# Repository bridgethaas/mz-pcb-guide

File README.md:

# mz-pcb-guide

Products of following along with the 'Designing a keyboard from scratch' guide at https://www.masterzen.fr/2020/05/03/designing-a-keyboard-part-1/

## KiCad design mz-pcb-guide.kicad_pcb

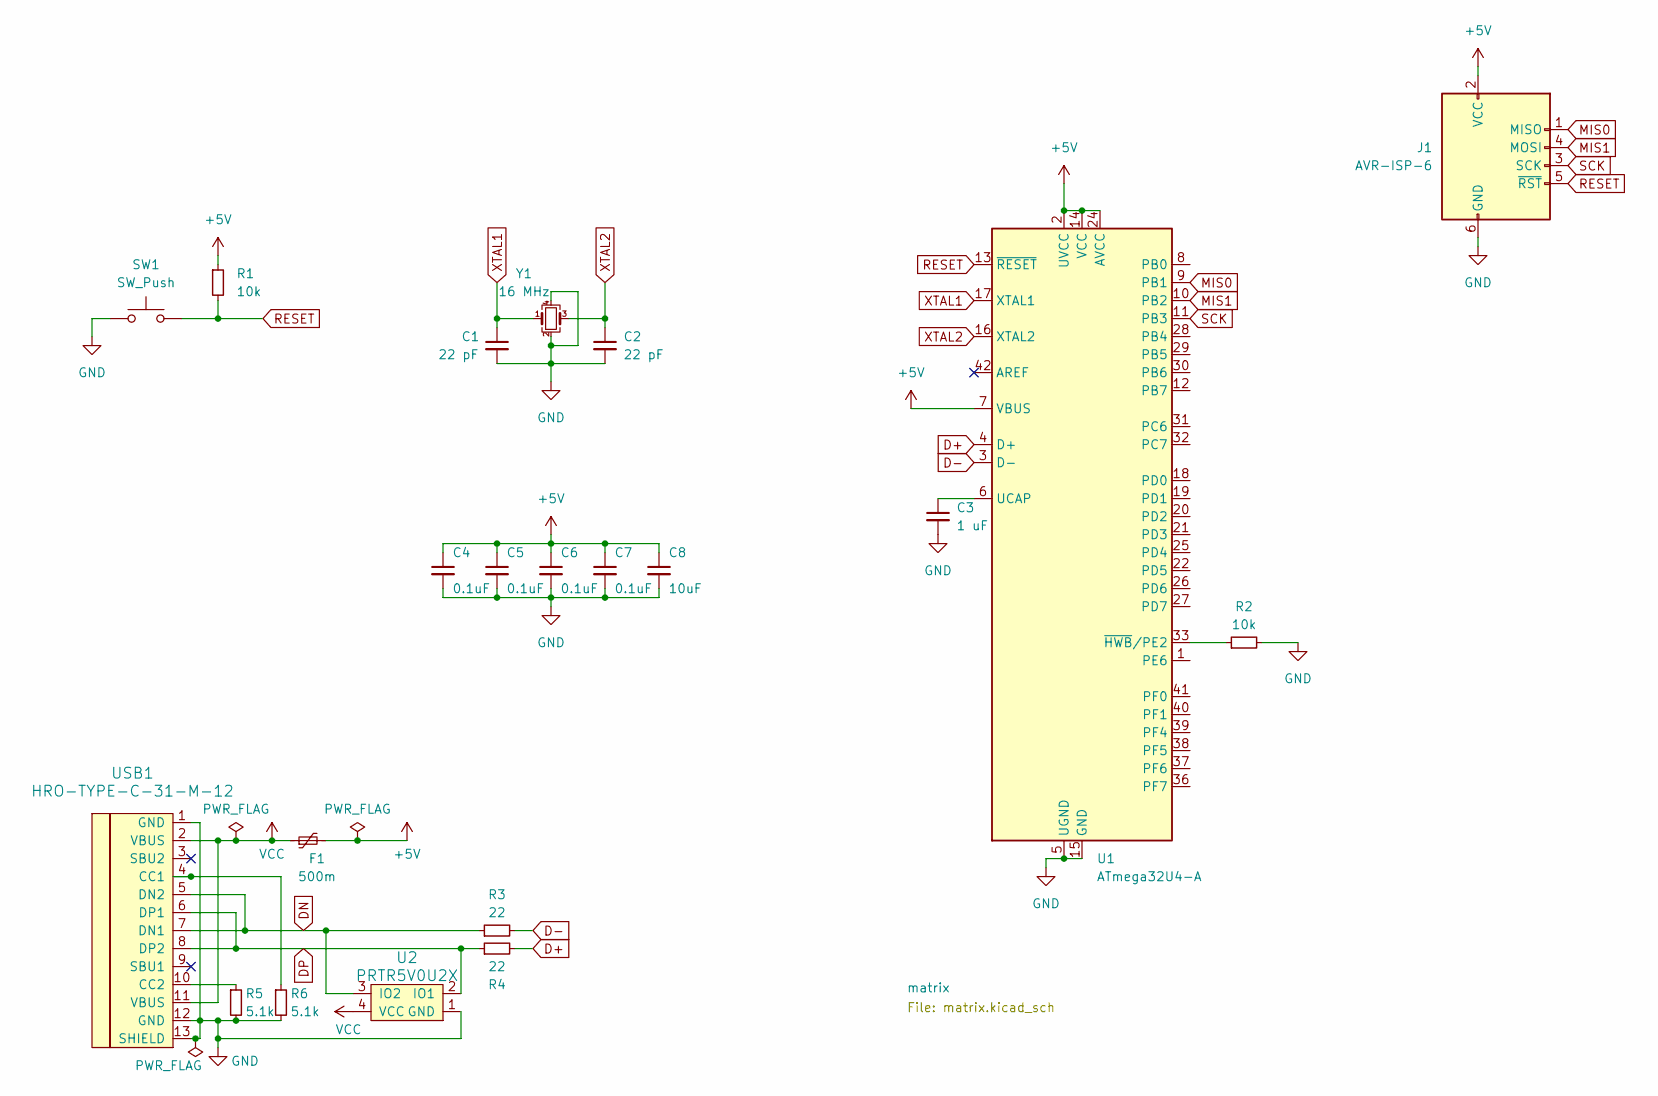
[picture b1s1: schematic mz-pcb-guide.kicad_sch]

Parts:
C1, C2: 22 pF; C_0805_2012Metric
C3: 1 uF; C_0805_2012Metric
C4, C5, C6, C7: 0.1uF; C_0805_2012Metric
C8: 10uF; C_0805_2012Metric
F1: 500m; Fuse_1206_3216Metric
J1: AVR-ISP-6; Reset_Pretty-Mask
R1, R2: 10k; R_0805_2012Metric
R3, R4: 22; R_0805_2012Metric
R5, R6: 5.1k; R_0805_2012Metric
SW1: SW_Push; SKQG-1155865
U1: ATmega32U4-A; TQFP-44_10x10mm_P0.8mm
U2: PRTR5V0U2X; SOT143B
USB1: HRO-TYPE-C-31-M-12
Y1: 16 MHz; Crystal_SMD_3225-4Pin_3.2x2.5mm

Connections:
+5V: C4.1, C5.1, C6.1, C7.1, C8.1, F1.2, J1.2 (VCC), R1.1, U1.2 (UVCC), U1.7 (VBUS), U1.14 (VCC), U1.24 (AVCC), U1.34 (VCC), U1.44 (AVCC)
D+: R4.2, U1.4 (D+)
D-: R3.2, U1.3 (D-)
DN: R3.1, U2.3 (IO2), USB1.5 (DN2), USB1.7 (DN1)
DP: R4.1, U2.2 (IO1), USB1.6 (DP1), USB1.8 (DP2)
GND: C1.2, C2.2, C3.2, C4.2, C5.2, C6.2, C7.2, C8.2, J1.6 (GND), R2.2, R5.2, R6.2, SW1.1, U1.5 (UGND), U1.15 (GND), U1.23 (GND), U1.35 (GND), U1.43 (GND), U2.1 (GND), USB1.1 (GND), USB1.12 (GND), USB1.13 (SHIELD), Y1.2, Y1.4
MIS0: J1.1 (MISO), U1.9 (PB1)
MIS1: J1.4 (MOSI), U1.10 (PB2)
unnamed: C3.1, U1.6 (UCAP)
unnamed: R2.1, U1.33 (~HWB/PE2)
unnamed: R5.1, USB1.10 (CC2)
unnamed: R6.1, USB1.4 (CC1)
RESET: J1.5 (~RST), R1.2, SW1.2, U1.13 (~RESET)
SCK: J1.3 (SCK), U1.11 (PB3)
VCC: F1.1, U2.4 (VCC), USB1.2 (VBUS), USB1.11 (VBUS)
XTAL1: C1.1, U1.17 (XTAL1), Y1.1
XTAL2: C2.1, U1.16 (XTAL2), Y1.3

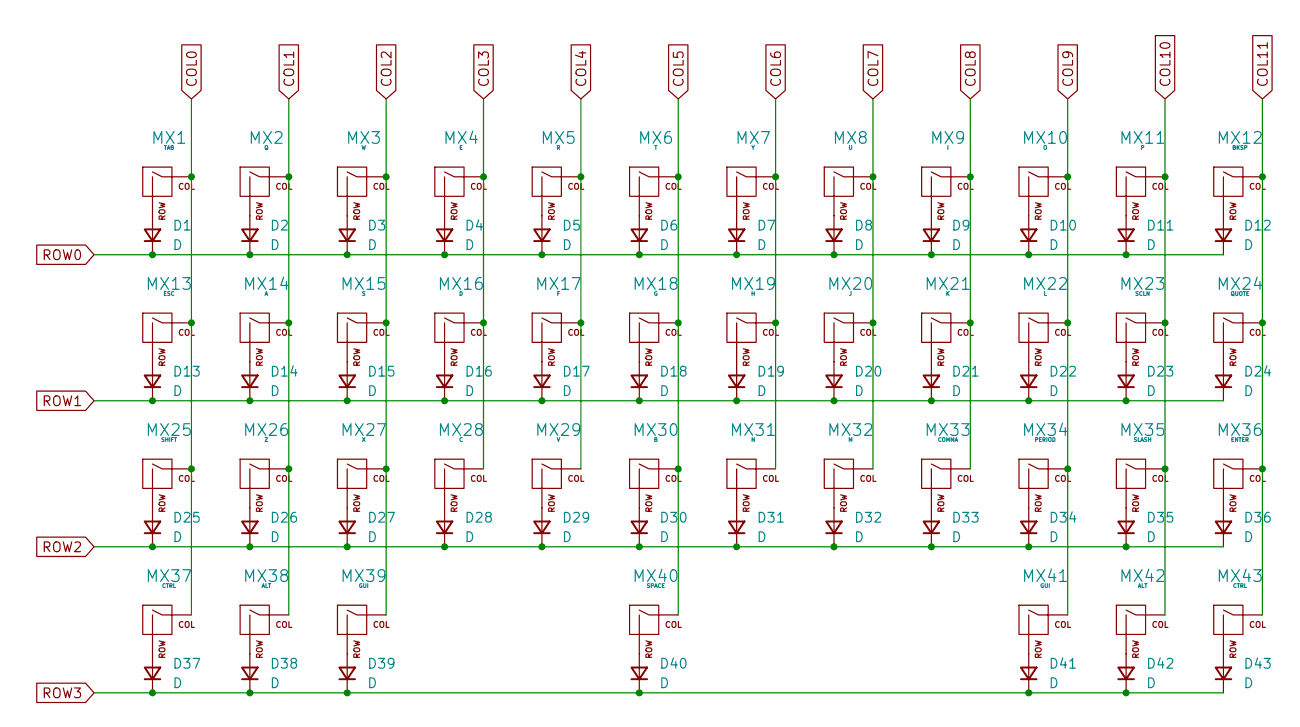
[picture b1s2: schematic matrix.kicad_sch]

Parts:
D1, D2, D3, D4, D5, D6, D7, D8, D9, D10, D11, D12, D13, D14, D15, D16, D17, D18, D19, D20, D21, D22, D23, D24, D25, D26, D27, D28, D29, D30, D31, D32, D33, D34, D35, D36, D37, D38, D39, D40, D41, D42, D43: D; D_0805_2012Metric
MX1: TAB; MXOnly-1U-NoLED
MX2: Q; MXOnly-1U-NoLED
MX3: W; MXOnly-1U-NoLED
MX4: E; MXOnly-1U-NoLED
MX5: R; MXOnly-1U-NoLED
MX6: T; MXOnly-1U-NoLED
MX7: Y; MXOnly-1U-NoLED
MX8: U; MXOnly-1U-NoLED
MX9: I; MXOnly-1U-NoLED
MX10: O; MXOnly-1U-NoLED
MX11: P; MXOnly-1U-NoLED
MX12: BKSP; MXOnly-1U-NoLED
MX13: ESC; MXOnly-1U-NoLED
MX14: A; MXOnly-1U-NoLED
MX15: S; MXOnly-1U-NoLED
MX16: D; MXOnly-1U-NoLED
MX17: F; MXOnly-1U-NoLED
MX18: G; MXOnly-1U-NoLED
MX19: H; MXOnly-1U-NoLED
MX20: J; MXOnly-1U-NoLED
MX21: K; MXOnly-1U-NoLED
MX22: L; MXOnly-1U-NoLED
MX23: SCLN; MXOnly-1U-NoLED
MX24: QUOTE; MXOnly-1U-NoLED
MX25: SHIFT; MXOnly-1U-NoLED
MX26: Z; MXOnly-1U-NoLED
MX27: X; MXOnly-1U-NoLED
MX28: C; MXOnly-1U-NoLED
MX29: V; MXOnly-1U-NoLED
MX30: B; MXOnly-1U-NoLED
MX31: N; MXOnly-1U-NoLED
MX32: M; MXOnly-1U-NoLED
MX33: COMMA; MXOnly-1U-NoLED
MX34: PERIOD; MXOnly-1U-NoLED
MX35: SLASH; MXOnly-1U-NoLED
MX36: ENTER; MXOnly-1U-NoLED
MX37, MX43: CTRL; MXOnly-1U-NoLED
MX38, MX42: ALT; MXOnly-1U-NoLED
MX39, MX41: GUI; MXOnly-1U-NoLED
MX40: SPACE; MXOnly-6U-Centered-NoLED

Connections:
COL0: MX1.1 (COL), MX13.1 (COL), MX25.1 (COL), MX37.1 (COL)
COL1: MX2.1 (COL), MX14.1 (COL), MX26.1 (COL), MX38.1 (COL)
COL2: MX3.1 (COL), MX15.1 (COL), MX27.1 (COL), MX39.1 (COL)
COL3: MX4.1 (COL), MX16.1 (COL), MX28.1 (COL)
COL4: MX5.1 (COL), MX17.1 (COL), MX29.1 (COL)
COL5: MX6.1 (COL), MX18.1 (COL), MX30.1 (COL), MX40.1 (COL)
COL6: MX7.1 (COL), MX19.1 (COL), MX31.1 (COL)
COL7: MX8.1 (COL), MX20.1 (COL), MX32.1 (COL)
COL8: MX9.1 (COL), MX21.1 (COL), MX33.1 (COL)
COL9: MX10.1 (COL), MX22.1 (COL), MX34.1 (COL), MX41.1 (COL)
COL10: MX11.1 (COL), MX23.1 (COL), MX35.1 (COL), MX42.1 (COL)
COL11: MX12.1 (COL), MX24.1 (COL), MX36.1 (COL), MX43.1 (COL)
unnamed: D1.2 (A), MX1.2 (ROW)
unnamed: D2.2 (A), MX2.2 (ROW)
unnamed: D3.2 (A), MX3.2 (ROW)
unnamed: D4.2 (A), MX4.2 (ROW)
unnamed: D5.2 (A), MX5.2 (ROW)
unnamed: D6.2 (A), MX6.2 (ROW)
unnamed: D7.2 (A), MX7.2 (ROW)
unnamed: D8.2 (A), MX8.2 (ROW)
unnamed: D9.2 (A), MX9.2 (ROW)
unnamed: D10.2 (A), MX10.2 (ROW)
unnamed: D11.2 (A), MX11.2 (ROW)
unnamed: D12.2 (A), MX12.2 (ROW)
unnamed: D13.2 (A), MX13.2 (ROW)
unnamed: D14.2 (A), MX14.2 (ROW)
unnamed: D15.2 (A), MX15.2 (ROW)
unnamed: D16.2 (A), MX16.2 (ROW)
unnamed: D17.2 (A), MX17.2 (ROW)
unnamed: D18.2 (A), MX18.2 (ROW)
unnamed: D19.2 (A), MX19.2 (ROW)
unnamed: D20.2 (A), MX20.2 (ROW)
unnamed: D21.2 (A), MX21.2 (ROW)
unnamed: D22.2 (A), MX22.2 (ROW)
unnamed: D23.2 (A), MX23.2 (ROW)
unnamed: D24.2 (A), MX24.2 (ROW)
unnamed: D25.2 (A), MX25.2 (ROW)
unnamed: D26.2 (A), MX26.2 (ROW)
unnamed: D27.2 (A), MX27.2 (ROW)
unnamed: D28.2 (A), MX28.2 (ROW)
unnamed: D29.2 (A), MX29.2 (ROW)
unnamed: D30.2 (A), MX30.2 (ROW)
unnamed: D31.2 (A), MX31.2 (ROW)
unnamed: D32.2 (A), MX32.2 (ROW)
unnamed: D33.2 (A), MX33.2 (ROW)
unnamed: D34.2 (A), MX34.2 (ROW)
unnamed: D35.2 (A), MX35.2 (ROW)
unnamed: D36.2 (A), MX36.2 (ROW)
unnamed: D37.2 (A), MX37.2 (ROW)
unnamed: D38.2 (A), MX38.2 (ROW)
unnamed: D39.2 (A), MX39.2 (ROW)
unnamed: D40.2 (A), MX40.2 (ROW)
unnamed: D41.2 (A), MX41.2 (ROW)
unnamed: D42.2 (A), MX42.2 (ROW)
unnamed: D43.2 (A), MX43.2 (ROW)
ROW0: D1.1 (K), D2.1 (K), D3.1 (K), D4.1 (K), D5.1 (K), D6.1 (K), D7.1 (K), D8.1 (K), D9.1 (K), D10.1 (K), D11.1 (K), D12.1 (K)
ROW1: D13.1 (K), D14.1 (K), D15.1 (K), D16.1 (K), D17.1 (K), D18.1 (K), D19.1 (K), D20.1 (K), D21.1 (K), D22.1 (K), D23.1 (K), D24.1 (K)
ROW2: D25.1 (K), D26.1 (K), D27.1 (K), D28.1 (K), D29.1 (K), D30.1 (K), D31.1 (K), D32.1 (K), D33.1 (K), D34.1 (K), D35.1 (K), D36.1 (K)
ROW3: D37.1 (K), D38.1 (K), D39.1 (K), D40.1 (K), D41.1 (K), D42.1 (K), D43.1 (K)

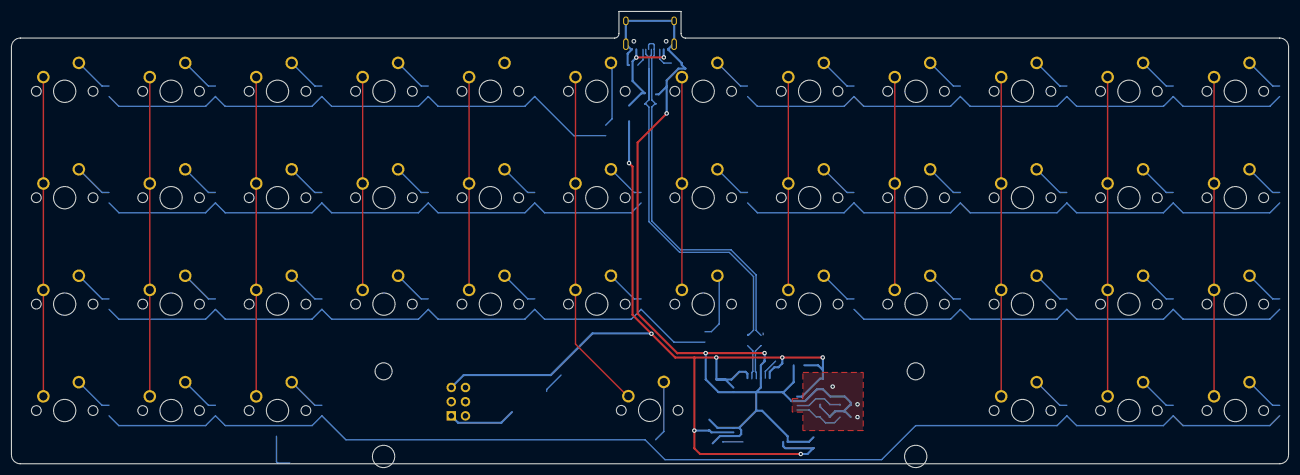
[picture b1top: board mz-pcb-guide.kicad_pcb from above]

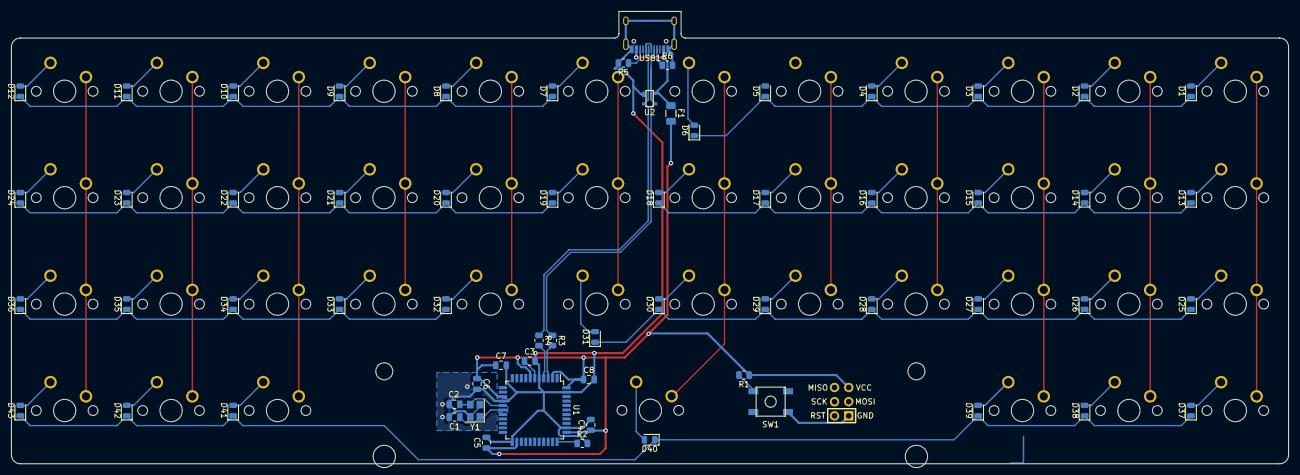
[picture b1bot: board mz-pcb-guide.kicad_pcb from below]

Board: 2 copper layers, 228.6 x 81.0 mm, 107 parts (64 on the bottom side), 76 nets.

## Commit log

2022-01-16 start readme
2022-01-16 added submodules for footprint libraries
2022-01-16 create kicad project
2022-01-16 include libraries in project
2022-01-17 add gitignore
2022-01-17 mcu, usb, isp header schematic
2022-01-18 finish matrix schema and assign footprints
2022-01-18 place switches and diodes
2022-01-18 place rest of components
2022-01-21 working on routing
2022-03-01 keebio component libraries
2022-03-01 new project subfolder
2022-03-11 finish schematic
